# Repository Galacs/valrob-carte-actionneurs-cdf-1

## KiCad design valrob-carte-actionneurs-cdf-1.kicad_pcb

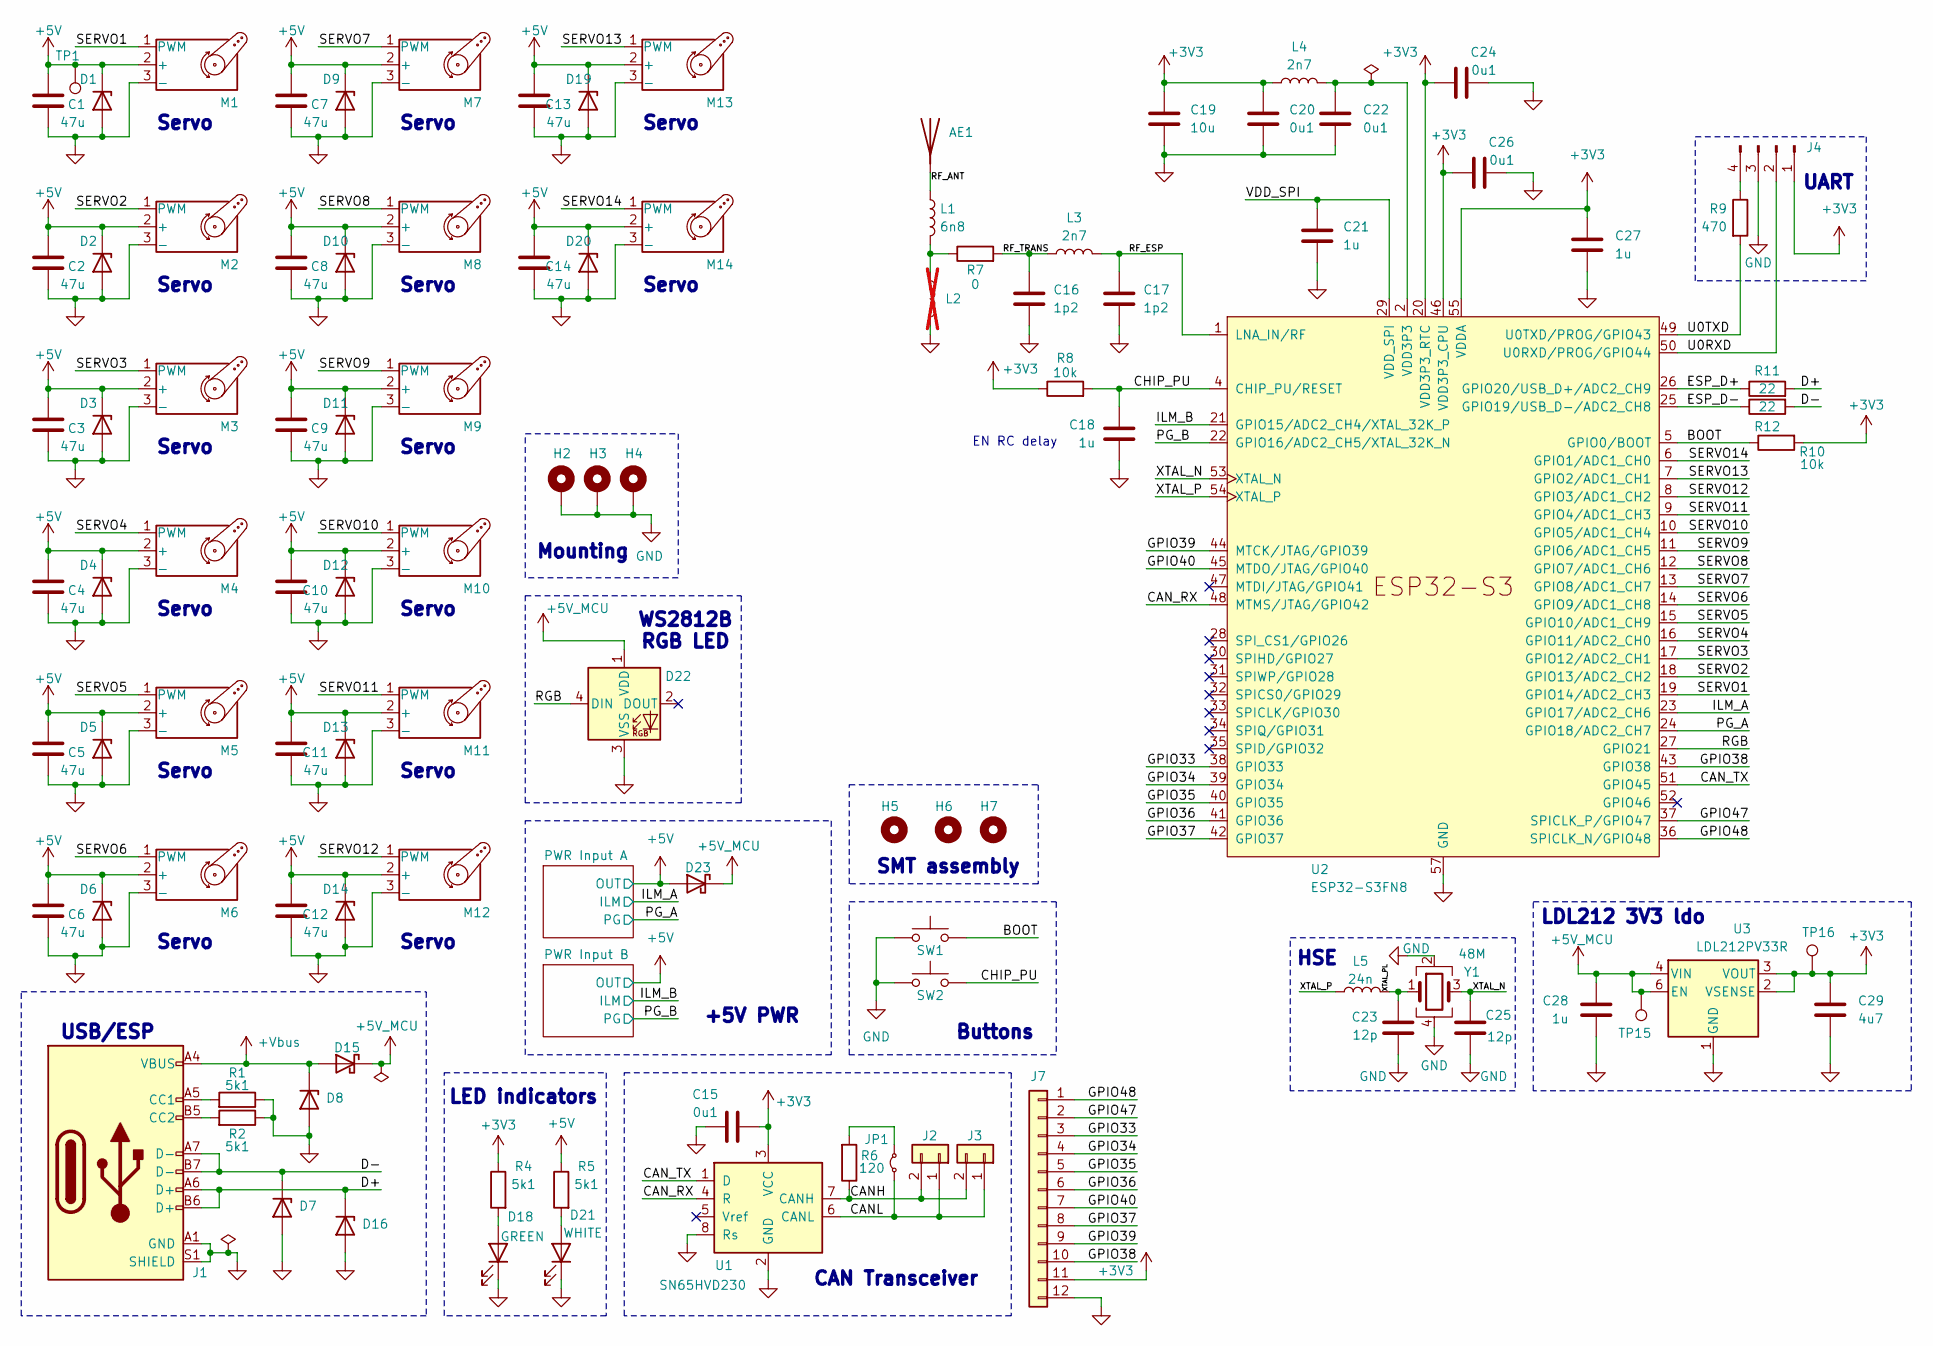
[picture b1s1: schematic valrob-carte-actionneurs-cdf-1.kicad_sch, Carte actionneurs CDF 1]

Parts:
AE1: Antenna; Johanson_2450AT18x100; Manufacturer Part Number RFANT3216120A5T; JLCPCB Part # C127629
C1, C2, C3, C4, C5, C6, C7, C8, C9, C10, C11, C12, C13, C14: 47u; C_1206_3216Metric; Manufacturer Part Number CL31A476MPHNNNE; JLCPCB Part # C96123
C15, C20, C22, C24, C26: 0u1; C_0402_1005Metric; Manufacturer Part Number CL05B104KB54PNC; JLCPCB Part # C307331
C16, C17: 1p2; C_0402_1005Metric; Manufacturer Part Number GJM1555C1H1R2WB01D; JLCPCB Part # C76899
C18, C21, C27, C28: 1u; C_0402_1005Metric; Manufacturer Part Number CL05A105KA5NQNC; JLCPCB Part # C52923
C19: 10u; C_0402_1005Metric; Manufacturer Part Number CL05A106MQ5NUNC; JLCPCB Part # C15525
C23, C25: 12p; C_0402_1005Metric; Manufacturer Part Number 0402CG120J500NT; JLCPCB Part # C1547
C29: 4u7; C_0402_1005Metric; Manufacturer Part Number CL05A475MP5NRNC; JLCPCB Part # C23733
D1, D2, D3, D4, D5, D6, D7, D8, D9, D10, D11, D12, D13, D14, D16, D19, D20: H5VU10U; Diode_DFN1006; Manufacturer Part Number H5VU10U; JLCPCB Part # C22395519
D15, D23: D_Schottky; D_SMA; Manufacturer Part Number SS54; JLCPCB Part # C22452
D18: GREEN; LED_0805_2012Metric; Manufacturer Part Number KT-0805G; JLCPCB Part # C2297
D21: WHITE; LED_0603_1608Metric; Manufacturer Part Number KT-0603W; JLCPCB Part # C2290
D22: WS2812B; LED_WS2812B_PLCC4_5.0x5.0mm_P3.2mm; Manufacturer Part Number WS2812B-V5/W; JLCPCB Part # C2874885
H2, H3, H4: MountingHole_Pad; MountingHole_2.2mm_M2_Pad_Via
H5, H6, H7: MountingHole; ToolingHole_1.152mm
J1: USB_C_Receptacle_USB2.0_14P; USB_C_Receptacle_HRO_TYPE-C-31-M-12; Manufacturer Part Number TYPE-C16PIN; JLCPCB Part # C393939
J2, J3: Conn_01x02; JST_XH_B2B-XH-A_1x02_P2.50mm_Vertical; Manufacturer Part Number B2B-XH-A(LF)(SN); JLCPCB Part # C158012
J4: Conn_01x04_Pin; PinHeader_1x04_P2.54mm_Vertical
J7: Conn_01x12; PinHeader_2x06_P2.54mm_Vertical
JP1: Jumper_2_Small_Bridged; SolderJumper-2_P1.3mm_Open_RoundedPad1.0x1.5mm
L1: 6n8; L_0402_1005Metric; Manufacturer Part Number LQG15HS6N8J02D; JLCPCB Part # C77110
L2: L; L_0402_1005Metric; not fitted
L3, L4: 2n7; L_0402_1005Metric; Manufacturer Part Number LQG15HS2N7S02D; JLCPCB Part # C77108
L5: 24n; L_0402_1005Metric; Manufacturer Part Number LQW15AN24NG00D; JLCPCB Part # C167472
M1, M2, M3, M4, M5, M6, M7, M8, M9, M10, M11, M12, M13, M14: Motor_Servo; PinHeader_1x03_P2.54mm_Vertical
R1, R2, R4, R5: 5k1; R_0402_1005Metric; Manufacturer Part Number 0402WGF5101TCE; JLCPCB Part # C25905
R6: 120; R_1206_3216Metric; Manufacturer Part Number 1206W4F1200T5E; JLCPCB Part # C17909
R7: 0; R_0402_1005Metric; Manufacturer Part Number 0402WGF0000TCE; JLCPCB Part # C17168
R8, R10: 10k; R_0402_1005Metric; Manufacturer Part Number 0402WGF1002TCE; JLCPCB Part # C25744
R9: 470; R_0402_1005Metric; Manufacturer Part Number 0402WGF4700TCE; JLCPCB Part # C25117
R11, R12: 22; R_0402_1005Metric; Manufacturer Part Number 0402WGF220JTCE; JLCPCB Part # C25092
SW1, SW2: SW_Push; SW_SPST_TS-1088-xR020; Manufacturer Part Number TS-1088-AR02016; JLCPCB Part # C720477
TP1, TP15, TP16: TestPoint; TestPoint_Pad_D2.0mm
U1: SN65HVD230; SOIC-8_3.9x4.9mm_P1.27mm; Manufacturer Part Number SN65HVD230DR; JLCPCB Part # C12084
U2: ESP32-S3FN8; QFN-56-1EP_7x7mm_P0.4mm_EP4x4mm_ThermalVias; Manufacturer Part Number ESP32-S3FH4R2; JLCPCB Part # C3013940
U3: LDL212PV33R; DFN-6-1EP_2x2mm_P0.5mm_ST; Manufacturer Part Number LDL212PV33R; JLCPCB Part # C2969892
Y1: 48M; Crystal_SMD_2016-4Pin_2.0x1.6mm; Manufacturer Part Number R940000096; JLCPCB Part # C7206306

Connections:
+3V3: C15.1, C19.1, C20.1, C24.1, C26.1, C27.1, C29.1, J4.1, J7.11, L4.1, R4.1, R8.1, R10.2, TP16.1 (1_1), U1.3 (VCC), U2.20 (VDD3P3_RTC), U2.46 (VDD3P3_CPU), U2.55 (VDDA), U2.56 (VDDA), U3.2 (VSENSE), U3.3 (VOUT); also elsewhere on the board
+5V: C1.1, C2.1, C3.1, C4.1, C5.1, C6.1, C7.1, C8.1, C9.1, C10.1, C11.1, C12.1, C13.1, C14.1, D1.1 (K), D2.1 (K), D3.1 (K), D4.1 (K), D5.1 (K), D6.1 (K), D9.1 (K), D10.1 (K), D11.1 (K), D12.1 (K), D13.1 (K), D14.1 (K), D19.1 (K), D20.1 (K), D23.2 (A), M1.2 (+), M2.2 (+), M3.2 (+), M4.2 (+), M5.2 (+), M6.2 (+), M7.2 (+), M8.2 (+), M9.2 (+), M10.2 (+), M11.2 (+), M12.2 (+), M13.2 (+), M14.2 (+), R5.1, TP1.1 (1_1); also elsewhere on the board
+5V_MCU: C28.1, D15.1 (K), D22.1 (VDD), D23.1 (K), TP15.1 (1_1), U3.4 (VIN), U3.6 (EN)
+Vbus: D8.1 (K), D15.2 (A), J1.A4 (VBUS), J1.A9 (VBUS), J1.B4 (VBUS), J1.B9 (VBUS)
/BOOT: R10.1, SW1.2, U2.5 (GPIO0/BOOT)
/CANH: J2.2, J3.2, R6.1, U1.7 (CANH)
/CANL: J2.1, J3.1, JP1.1 (A), U1.6 (CANL)
/CAN_RX: U1.4 (R), U2.48 (MTMS/JTAG/GPIO42)
/CAN_TX: U1.1 (D), U2.51 (GPIO45)
/CHIP_PU: C18.1, R8.2, SW2.2, U2.4 (CHIP_PU/RESET)
/D+: D16.1 (K), J1.A6 (D+), J1.B6 (D+), R11.2
/D-: D7.1 (K), J1.A7 (D-), J1.B7 (D-), R12.2
/ESP_D+: R11.1, U2.26 (GPIO20/USB_D+/ADC2_CH9)
/ESP_D-: R12.1, U2.25 (GPIO19/USB_D-/ADC2_CH8)
/GPIO33: J7.3, U2.38 (GPIO33)
/GPIO34: J7.4, U2.39 (GPIO34)
/GPIO35: J7.5, U2.40 (GPIO35)
/GPIO36: J7.6, U2.41 (GPIO36)
/GPIO37: J7.8, U2.42 (GPIO37)
/GPIO38: J7.10, U2.43 (GPIO38)
/GPIO39: J7.9, U2.44 (MTCK/JTAG/GPIO39)
/GPIO40: J7.7, U2.45 (MTDO/JTAG/GPIO40)
/GPIO47: J7.2, U2.37 (SPICLK_P/GPIO47)
/GPIO48: J7.1, U2.36 (SPICLK_N/GPIO48)
/ILM_A: U2.23 (GPIO17/ADC2_CH6); also elsewhere on the board
/ILM_B: U2.21 (GPIO15/ADC2_CH4/XTAL_32K_P); also elsewhere on the board
/PG_A: U2.24 (GPIO18/ADC2_CH7); also elsewhere on the board
/PG_B: U2.22 (GPIO16/ADC2_CH5/XTAL_32K_N); also elsewhere on the board
/RF_ANT: AE1.1 (A_1), L1.1
/RF_ESP: C17.1, L3.2, U2.1 (LNA_IN/RF)
/RF_TRANS: C16.1, L3.1, R7.2
/RGB: D22.4 (DIN), U2.27 (GPIO21)
/SERVO1: M1.1 (PWM), U2.19 (GPIO14/ADC2_CH3)
/SERVO2: M2.1 (PWM), U2.18 (GPIO13/ADC2_CH2)
/SERVO3: M3.1 (PWM), U2.17 (GPIO12/ADC2_CH1)
/SERVO4: M4.1 (PWM), U2.16 (GPIO11/ADC2_CH0)
/SERVO5: M5.1 (PWM), U2.15 (GPIO10/ADC1_CH9)
/SERVO6: M6.1 (PWM), U2.14 (GPIO9/ADC1_CH8)
/SERVO7: M7.1 (PWM), U2.13 (GPIO8/ADC1_CH7)
/SERVO8: M8.1 (PWM), U2.12 (GPIO7/ADC1_CH6)
/SERVO9: M9.1 (PWM), U2.11 (GPIO6/ADC1_CH5)
/SERVO10: M10.1 (PWM), U2.10 (GPIO5/ADC1_CH4)
/SERVO11: M11.1 (PWM), U2.9 (GPIO4/ADC1_CH3)
/SERVO12: M12.1 (PWM), U2.8 (GPIO3/ADC1_CH2)
/SERVO13: M13.1 (PWM), U2.7 (GPIO2/ADC1_CH1)
/SERVO14: M14.1 (PWM), U2.6 (GPIO1/ADC1_CH0)
/U0RXD: J4.2, U2.50 (U0RXD/PROG/GPIO44)
/U0TXD: R9.2, U2.49 (U0TXD/PROG/GPIO43)
/VDD_SPI: C21.1, U2.29 (VDD_SPI)
/XTAL_N: C25.1, U2.53 (XTAL_N), Y1.3
/XTAL_P: L5.1, U2.54 (XTAL_P)
/XTAL_PL: C23.2, L5.2, Y1.1
GND: C1.2, C2.2, C3.2, C4.2, C5.2, C6.2, C7.2, C8.2, C9.2, C10.2, C11.2, C12.2, C13.2, C14.2, C15.2, C16.2, C17.2, C18.2, C19.2, C20.2, C21.2, C22.2, C23.1, C24.2, C25.2, C26.2, C27.2, C28.2, C29.2, D1.2 (A), D2.2 (A), D3.2 (A), D4.2 (A), D5.2 (A), D6.2 (A), D7.2 (A), D8.2 (A), D9.2 (A), D10.2 (A), D11.2 (A), D12.2 (A), D13.2 (A), D14.2 (A), D16.2 (A), D18.1 (K), D19.2 (A), D20.2 (A), D21.1 (K), D22.3 (VSS), H2.1 (1_1), H3.1 (1_1), H4.1 (1_1), J1.A1 (GND), J1.A12 (GND), J1.B1 (GND), J1.B12 (GND), J1.S1 (SHIELD), J4.3, J7.12, L2.2, M1.3 (-), M2.3 (-), M3.3 (-), M4.3 (-), M5.3 (-), M6.3 (-), M7.3 (-), M8.3 (-), M9.3 (-), M10.3 (-), M11.3 (-), M12.3 (-), M13.3 (-), M14.3 (-), R1.1, R2.1, SW1.1, SW2.1, U1.2 (GND), U1.8 (Rs), U2.57 (GND), U3.1 (GND), Y1.2, Y1.4; also elsewhere on the board
unnamed: D18.2 (A), R4.2
unnamed: D21.2 (A), R5.2
unnamed: J1.A5 (CC1), R1.2
unnamed: J1.B5 (CC2), R2.2
unnamed: J4.4, R9.1
unnamed: JP1.2 (B), R6.2
unnamed: L1.2, L2.1, R7.1
VDD3P3: C22.1, L4.2, U2.2 (VDD3P3), U2.3 (VDD3P3)

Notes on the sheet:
WS2812B RGB LED
USB/ESP
Servo
CAN Transceiver
UART
Mounting
LDL212 3V3 ldo
Buttons
SMT assembly
HSE
+5V PWR
LED indicators
EN RC delay

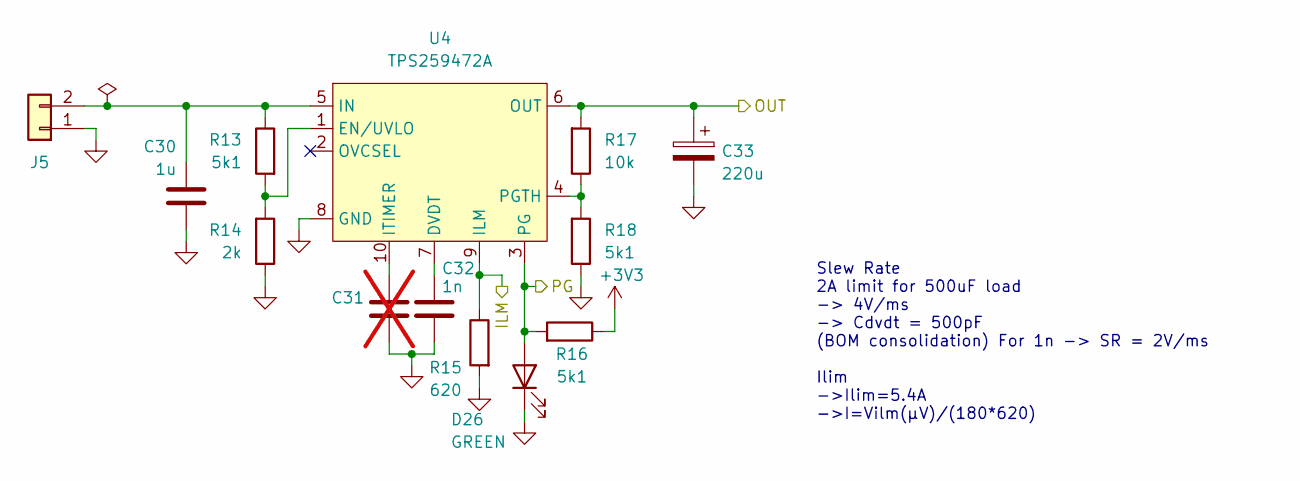
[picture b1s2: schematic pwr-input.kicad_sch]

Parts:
C30: 1u; C_0402_1005Metric; Manufacturer Part Number CL05A105KA5NQNC; JLCPCB Part # C52923
C31: C; C_0402_1005Metric; not fitted
C32: 1n; C_0402_1005Metric; Manufacturer Part Number 0402B102K500NT; JLCPCB Part # C1523
C33: 220u; CP_Elec_6.3x7.7; Manufacturer Part Number RVT1E221M0607; JLCPCB Part # C2918361
D26: GREEN; LED_0805_2012Metric; Manufacturer Part Number KT-0805G; JLCPCB Part # C2297
J5: Conn_01x02; JST_XH_B2B-XH-A_1x02_P2.50mm_Vertical; Manufacturer Part Number B2B-XH-A(LF)(SN); JLCPCB Part # C158012
R13, R16, R18: 5k1; R_0402_1005Metric; Manufacturer Part Number 0402WGF5101TCE; JLCPCB Part # C25905
R14: 2k; R_0402_1005Metric; Manufacturer Part Number 0402WGF2001TCE; JLCPCB Part # C4109
R15: 620; R_0402_1005Metric; Manufacturer Part Number 0402WGF6200TCE; JLCPCB Part # C4961
R17: 10k; R_0402_1005Metric; Manufacturer Part Number 0402WGF1002TCE; JLCPCB Part # C25744
U4: TPS259472A; Texas_RPW0010A_VQFN-HR-10_2x2mm_P0.5mm; Manufacturer Part Number TPS259472ARPWR; JLCPCB Part # C3662789

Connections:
+3V3: R16.1; also elsewhere on the board
+5V: C33.1, R17.2, U4.6 (OUT); also elsewhere on the board
/ILM_B: R15.1, U4.9 (ILM); also elsewhere on the board
/PG_B: D26.2 (A), R16.2, U4.3 (PG); also elsewhere on the board
GND: C30.1, C31.2, C32.2, C33.2, D26.1 (K), J5.1, R14.1, R15.2, R18.1, U4.8 (GND); also elsewhere on the board
unnamed: C30.2, J5.2, R13.1, U4.5 (IN)
unnamed: C32.1, U4.7 (DVDT)
unnamed: R13.2, R14.2, U4.1 (EN/UVLO)
unnamed: C31.1, U4.10 (ITIMER)
unnamed: R17.1, R18.2, U4.4 (PGTH)

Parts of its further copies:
C35: 1u; C_0402_1005Metric; Manufacturer Part Number CL05A105KA5NQNC; JLCPCB Part # C52923
C36: C; C_0402_1005Metric; not fitted
C37: 1n; C_0402_1005Metric; Manufacturer Part Number 0402B102K500NT; JLCPCB Part # C1523
C38: 220u; CP_Elec_6.3x7.7; Manufacturer Part Number RVT1E221M0607; JLCPCB Part # C2918361
D27: GREEN; LED_0805_2012Metric; Manufacturer Part Number KT-0805G; JLCPCB Part # C2297
J6: Conn_01x02; JST_XH_B2B-XH-A_1x02_P2.50mm_Vertical; Manufacturer Part Number B2B-XH-A(LF)(SN); JLCPCB Part # C158012
R19, R22, R24: 5k1; R_0402_1005Metric; Manufacturer Part Number 0402WGF5101TCE; JLCPCB Part # C25905
R20: 2k; R_0402_1005Metric; Manufacturer Part Number 0402WGF2001TCE; JLCPCB Part # C4109
R21: 620; R_0402_1005Metric; Manufacturer Part Number 0402WGF6200TCE; JLCPCB Part # C4961
R23: 10k; R_0402_1005Metric; Manufacturer Part Number 0402WGF1002TCE; JLCPCB Part # C25744
U5: TPS259472A; Texas_RPW0010A_VQFN-HR-10_2x2mm_P0.5mm; Manufacturer Part Number TPS259472ARPWR; JLCPCB Part # C3662789

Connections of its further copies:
+3V3: R22.1; also elsewhere on the board
+5V: C38.1, R23.2, U5.6 (OUT); also elsewhere on the board
/ILM_A: R21.1, U5.9 (ILM); also elsewhere on the board
/PG_A: D27.2 (A), R22.2, U5.3 (PG); also elsewhere on the board
GND: C35.1, C36.2, C37.2, C38.2, D27.1 (K), J6.1, R20.1, R21.2, R24.1, U5.8 (GND); also elsewhere on the board
unnamed: C35.2, J6.2, R19.1, U5.5 (IN)
unnamed: C37.1, U5.7 (DVDT)
unnamed: R19.2, R20.2, U5.1 (EN/UVLO)
unnamed: C36.1, U5.10 (ITIMER)
unnamed: R23.1, R24.2, U5.4 (PGTH)

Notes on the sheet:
Slew Rate 2A limit for 500uF load -> 4V/ms -> Cdvdt = 500pF (BOM consolidation) For 1n -> SR = 2V/ms Ilim ->Ilim=5.4A ->I=Vilm(µV)/(180*620)

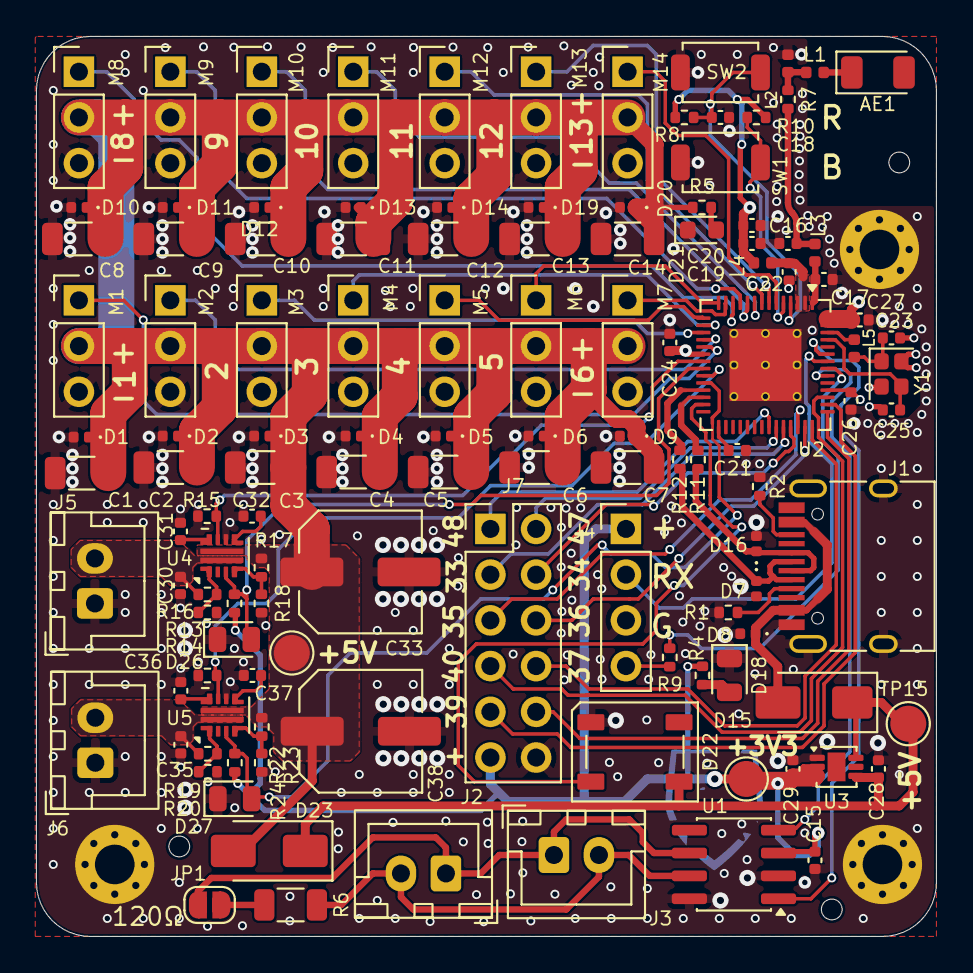
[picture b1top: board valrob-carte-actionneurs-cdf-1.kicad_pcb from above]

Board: 4 copper layers, 50.0 x 50.0 mm, 129 parts (0 on the bottom side), 71 nets.

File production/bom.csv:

Designator,Footprint,Quantity,Value,LCSC Part #
AE1,Johanson_2450AT18x100,1,Antenna,C127629
"C1, C10, C11, C12, C13, C14, C2, C3, C4, C5, C6, C7, C8, C9",1206,14,47u,C96123
"C15, C20, C22, C24, C26",0402,5,0u1,C307331
"C16, C17",0402,2,1p2,C76899
"C18, C21, C27, C28, C30, C35",0402,6,1u,C52923
C19,0402,1,10u,C15525
"C23, C25",0402,2,12p,C1547
C29,0402,1,4u7,C23733
"C32, C37",0402,2,1n,C1523
"C33, C38",CP_Elec_6.3x7.7,2,220u,C2918361
"D1, D10, D11, D12, D13, D14, D16, D19, D2, D20, D3, D4, D5, D6, D7, D8, D9",Diode_DFN1006,17,H5VU10U,C22395519
"D15, D23",D_SMA,2,D_Schottky,C22452
"D18, D26, D27",0805,3,GREEN,C2297
D21,0603,1,WHITE,C2290
D22,LED_WS2812B_PLCC4_5.0x5.0mm_P3.2mm,1,WS2812B,C2874885
J1,USB_C_Receptacle_HRO_TYPE-C-31-M-12,1,USB_C_Receptacle_USB2.0_14P,C393939
"J2, J3, J5, J6",JST_XH_B2B-XH-A_1x02_P2.50mm_Vertical,4,Conn_01x02,C158012
J7,PinHeader_2x06_P2.54mm_Vertical,1,Conn_01x12,
L1,0402,1,6n8,C77110
"L3, L4",0402,2,2n7,C77108
L5,0402,1,24n,C167472
"R1, R13, R16, R18, R19, R2, R22, R24, R4, R5",0402,10,5k1,C25905
"R10, R17, R23, R8",0402,4,10k,C25744
"R11, R12",0402,2,22,C25092
"R14, R20",0402,2,2k,C4109
"R15, R21",0402,2,620,C4961
R6,1206,1,120,C17909
R7,0402,1,0,C17168
R9,0402,1,470,C25117
"SW1, SW2",SW_SPST_TS-1088-xR020,2,SW_Push,C720477
U1,SOIC-8_3.9x4.9mm_P1.27mm,1,SN65HVD230,C12084
U2,QFN-56-1EP_7x7mm_P0.4mm_EP4x4mm_ThermalVias,1,ESP32-S3FN8,C3013940
U3,DFN-6-1EP_2x2mm_P0.5mm_ST,1,LDL212PV33R,C2969892
"U4, U5",Texas_RPW0010A_VQFN-HR-10_2x2mm_P0.5mm,2,TPS259472A,C3662789
Y1,Crystal_SMD_2016-4Pin_2.0x1.6mm,1,48M,C7206306

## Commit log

2026-02-17 schem: import esp32s3 from valrob-pami
2026-02-17 schem: import esp32 HSE crystal
2026-02-17 schem: add USB c connector
2026-02-17 schem: add servo connector
2026-02-17 schem: add led indicators
2026-02-17 schem: import LDL212 3V3 ldo
2026-02-17 schem: add TPS259472A 5v power input efuse
2026-02-17 schem: update efuse to work as downstream
2026-02-17 schem: configure efuse
2026-02-18 schem: add dual 5v pwr inputs
2026-02-18 schem: add status rgb leds
2026-02-18 schem: add dual port can transceiver
2026-02-18 schem: add 5v rail status leds
2026-02-18 schem: reorganize
2026-02-18 schem: connect peripherals gpios
2026-02-18 schem: add CHIP_PU and BOOT buttons
2026-02-18 schem: add test points
2026-02-18 schem: add 14 servo channels
2026-02-18 schem: run and fix ERC
2026-02-18 schem: import net classes
2026-02-18 schem: fix BOM
2026-02-18 schem: add sheet title
2026-02-18 schem: reannotate
2026-02-18 pcb: import pcb stackup and constraints
2026-02-18 pcb: import footprints from schem
2026-02-18 pcb: import missing 3d models
2026-02-18 schem/pcb: use TPS efuses ORing configuration
2026-02-18 schem: remove 5v input bulk cap
2026-02-18 pcb: add 2x TPS25947 layout
2026-02-18 pcb: add USB C initial layout
2026-02-18 pcb: add LDL212 3V3 ldo initial layout
2026-02-18 schem: remove extra test points
2026-02-18 schem: add servo components classes
2026-02-18 pcb: initial servo routing
2026-02-19 schem: add servo initial layout
2026-02-19 pcb: add initial layout
2026-02-20 schem: remove one rgb led
2026-02-20 schem: remove extra power indicator led
2026-02-20 pcb: add board outline
2026-02-20 schem: add mounting holes
2026-02-20 pcb: add initial component placement
2026-02-20 schem: add extra GPIOs header
2026-02-20 pcb: add gpio header
2026-02-21 pcb: line up gpio to 2.54 grid
2026-02-21 pcb: layout refinement
2026-02-21 pcb: add gnd planes
2026-02-21 pcb: add gnd vias
2026-02-21 pcb: add drill/place origin
2026-02-21 schem: reorganize programmable GPIOs
2026-02-21 pcb: add rf routing
2026-02-21 pcb: add crystal routing
2026-02-21 pcb: add usb routing
2026-02-21 pcb: add can routing
2026-02-21 pcb: add UART routing
2026-02-21 pcb: add servo 5V routing
2026-02-21 pcb: add efuse and 5v pwr routing
2026-02-21 pcb: add servo PWM routing
2026-02-21 pcb: add usb c routing
2026-02-21 pcb: add BOOT and CHIP_PU routing
2026-02-21 pcb: add spare GPIOs routing
2026-02-21 pcb: add efuse mcu routing
2026-02-21 pcb: add RGB led routing
2026-02-21 pcb: add 3v3 pwr routing
2026-02-21 pcb: add stitching vias
2026-02-21 pcb: run and fix DRC
2026-02-21 pcb: remove unused internal pads
2026-02-21 pcb: clean up silkscreen
2026-02-21 pcb: add user txt
2026-02-21 schem: add erc efuse output exlusion
2026-02-21 generate production files
2026-02-23 add jlcjlc placeholder and regenerate production files
2026-03-10 pcb: add title
2026-03-10 pcb: add step export settings
2026-04-12 schem/pcb: update to kicad 10
2026-04-12 schem/pcb: add smt tooling holes
2026-04-12 regenerate production files
2026-04-12 remove old production file
